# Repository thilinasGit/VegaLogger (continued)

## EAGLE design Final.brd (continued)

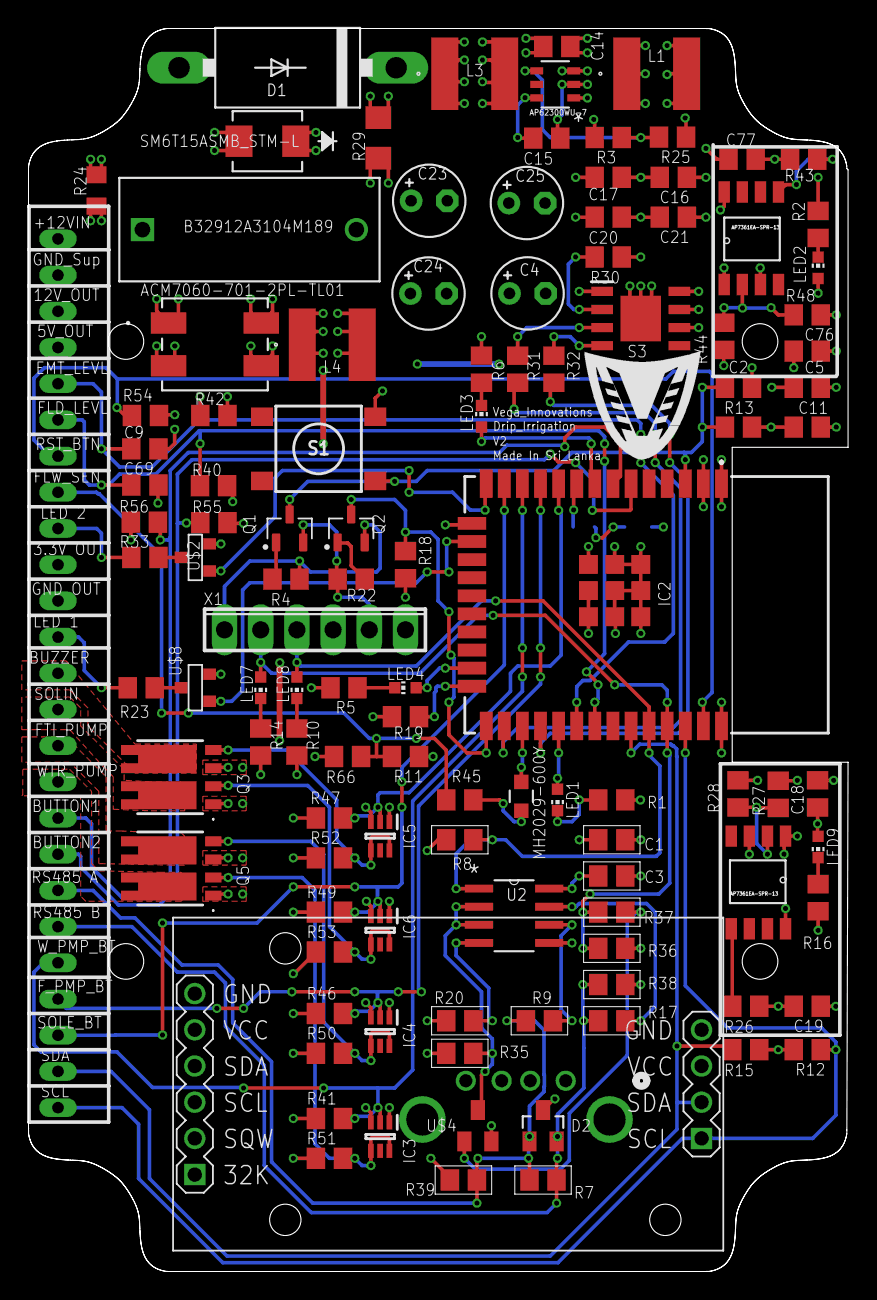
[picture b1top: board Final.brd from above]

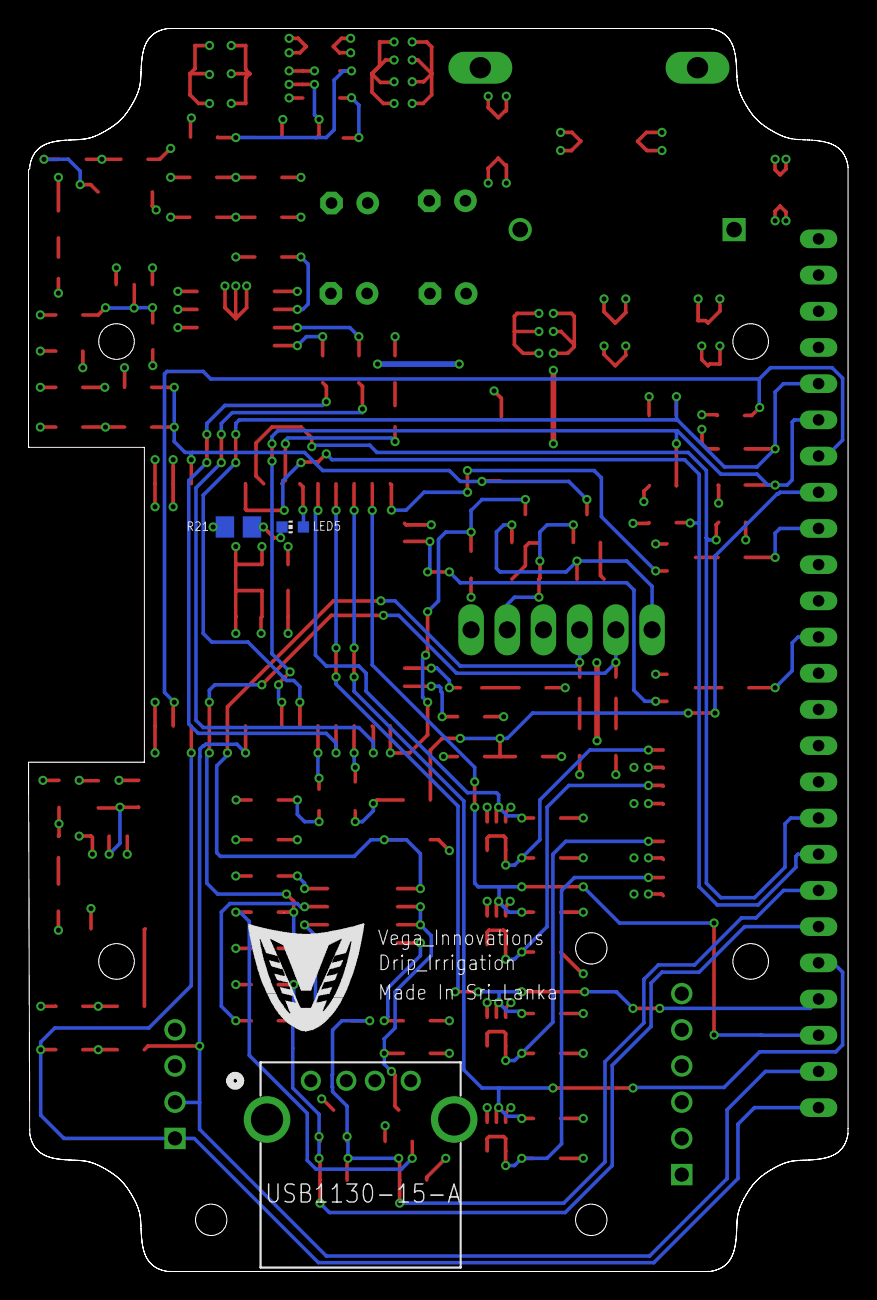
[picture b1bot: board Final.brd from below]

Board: 4 copper layers, 57.5 x 87.2 mm, 116 parts (3 on the bottom side), 80 nets.

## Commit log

2023-08-29 Create ExternStuff
2023-09-08 Update VegaLogger.ino
    added sharedpreferences
    todo
    debug shared preferences
    add non blocking call to reconnect
2023-09-13 Update VegaLogger.ino
    not working
2023-10-17 VegaLogger.ino
    v 2.7
2023-10-18 Added files
2023-11-08 fixed bugs
2024-02-21 Update VegaLogger.ino
    Removed mqtt topic
2024-02-21 Update mqtt_client_sub.py
    Removed mqtt topic
2024-02-21 Update mqtt_subscribe.php
    Mqtt topic removed
